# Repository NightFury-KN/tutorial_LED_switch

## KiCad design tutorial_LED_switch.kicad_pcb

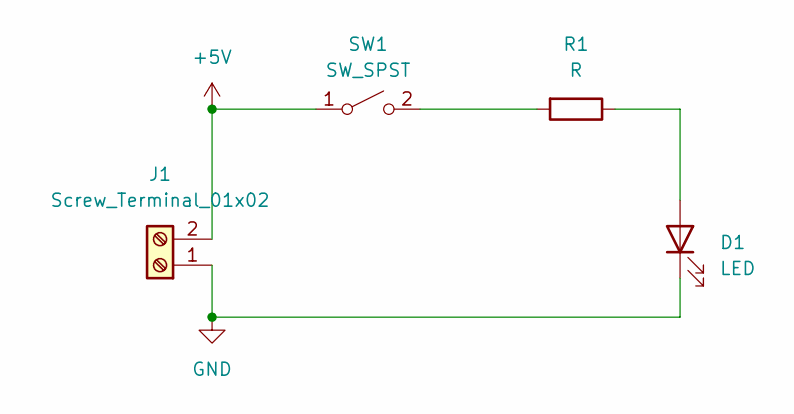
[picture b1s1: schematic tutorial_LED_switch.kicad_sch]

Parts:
D1: LED
J1: Screw_Terminal_01x02
R1: R
SW1: SW_SPST

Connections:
+5V: J1.2, SW1.1 (A)
GND: D1.1 (K), J1.1
unnamed: D1.2 (A), R1.1
unnamed: R1.2, SW1.2 (B)

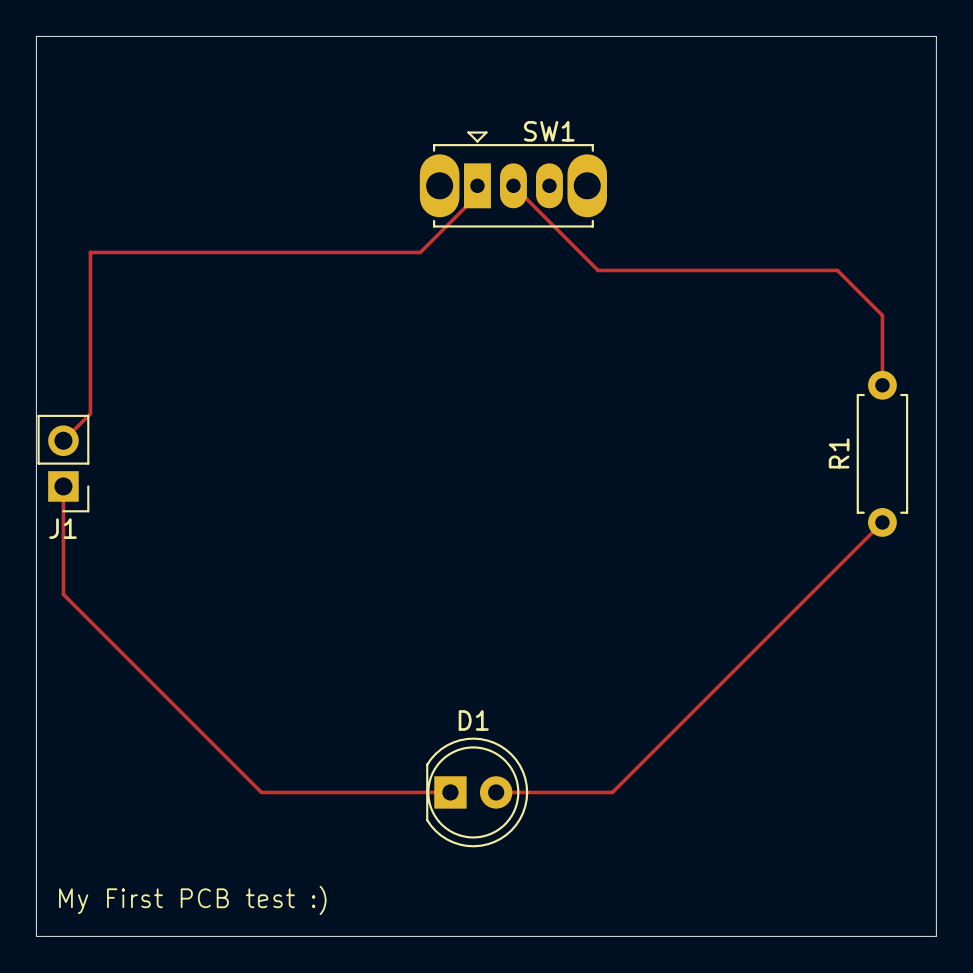
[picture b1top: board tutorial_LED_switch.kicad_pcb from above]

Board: 2 copper layers, 50.0 x 50.0 mm, 4 parts (0 on the bottom side), 4 nets.

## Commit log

2025-12-03 Initial KiCad project
2025-12-03 test commit
